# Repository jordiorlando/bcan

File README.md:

# bcan
### Beacon Controlled Autonomous Network

This project aims to create a semi-autonomous model train capable of detecting and avoiding obstacles. It makes use of small IR beacons placed between the rails to transmit a unique ID that can be mapped to various train functions, such as speed or lighting.

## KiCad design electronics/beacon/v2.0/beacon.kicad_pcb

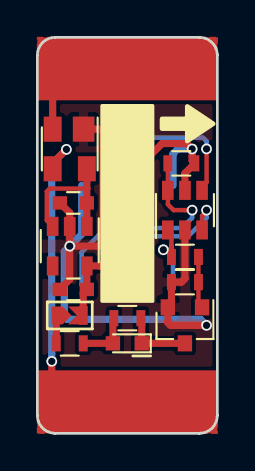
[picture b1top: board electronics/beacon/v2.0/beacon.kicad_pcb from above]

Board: 2 copper layers, 10.0 x 22.0 mm, 16 parts (1 on the bottom side), 13 nets.

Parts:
C1: 10u; C_0603
C2: 1u; C_0603
D1: IR; LED_0603
D2: BAS4002A; SOT-143
J1: L; Pad_Length10mm_Width3.5mm
J2: R; Pad_Length10mm_Width3.5mm
J3: TPI; Pin_Header_Straight_2x03_Pitch2.54mm_SMD
JP1: +1V8; Solder_Jumper_NC_Small
Q1: BSS138; SOT-23
R1, R3: 10k; R_0603
R2: 100; R_0603
R4: 47; R_0603
R5: R; R_0603
U1: ATTINY10-TS; SOT-23-6
U2: MIC5225-1.8YM5; SOT-23-5

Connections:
+1V8: C2.1, J3.2, JP1.2, R1.1, U1.5, U2.5
/PB0: J3.1, R2.1, U1.1
/PB1: J3.3, U1.3
/PB2: J3.4, U1.4
/RAIL_L: D2.2, J1.1
/RAIL_R: D2.3, J2.1
/~RST: J3.5, R1.2, U1.6
GND: C1.2, C2.2, D2.1, J3.6, Q1.2, R3.2, U1.2, U2.2
unnamed: D1.1, Q1.3, R5.2
unnamed: D1.2, R4.2, R5.1
unnamed: JP1.1, R4.1
unnamed: Q1.1, R2.2, R3.1
VCC: C1.1, D2.4, U2.1, U2.3

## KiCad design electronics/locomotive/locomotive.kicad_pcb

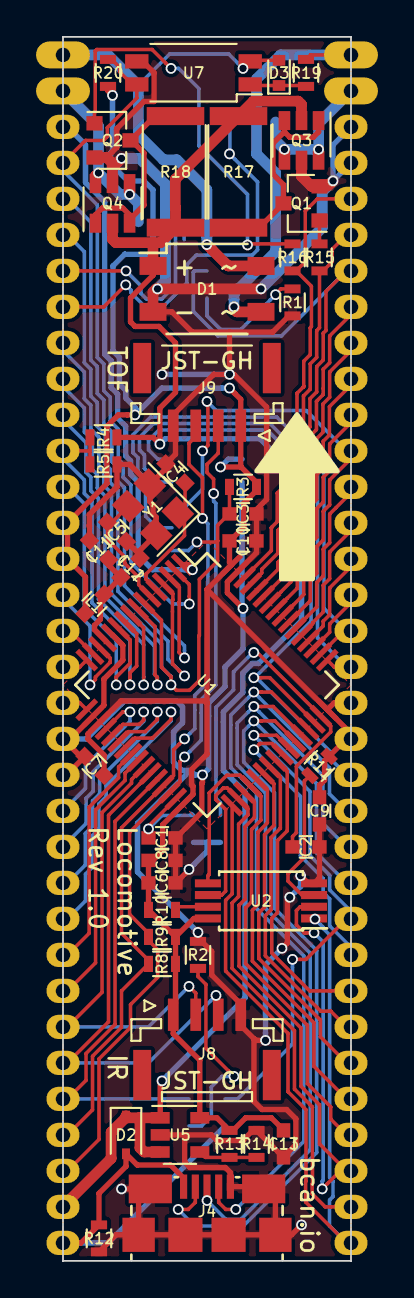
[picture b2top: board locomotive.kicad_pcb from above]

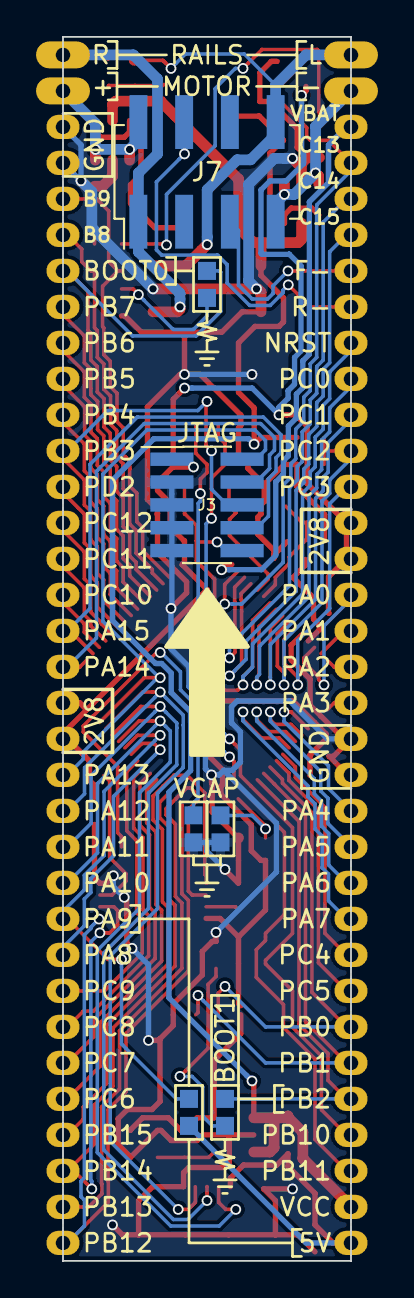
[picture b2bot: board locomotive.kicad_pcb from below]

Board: 2 copper layers, 16.0 x 68.0 mm, 58 parts (7 on the bottom side), 77 nets.

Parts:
C1, C2, C13: 2u2; C_0603
C3, C7, C8, C9, C10, C11: 100n; C_0603
C4, C5: 10p; C_0603
C6: 4u7; C_0603
C12: 1u; C_0603
D1: CDBHM240L-HF; TO-269AA
D2: CUS08F30; D_SOD-323
D3: 1N4148; D_SOD-523
J1: PIN[1..32]; Castellations_1x32_Pitch2.00mm
J2: PIN[33..64]; Castellations_1x32_Pitch2.00mm
J3: JTAG; Pin_Header_Straight_2x05_Pitch1.27mm_SMD
J4: USB_OTG; USB_Micro-B_Amphenol_10118192
J5: RAILS; Castellations_1x02_Pitch2.00mm
J6: MOTOR; Castellations_1x02_Pitch2.00mm
J7: TRAIN; Pin_Header_Straight_2x04_Pitch2.54mm_SMD
J8: IR; JST_GH_BM04B-GHS-TBT_04x1.25mm_Straight
J9: TOF; JST_GH_SM04B-GHS-TB_04x1.25mm_Angled
JP1: BOOT0; Solder_Jumper_NC
JP2: BOOT1; Solder_Jumper_NC
JP3: VCAP1; Solder_Jumper_NO
JP4: VCAP2; Solder_Jumper_NO
JP5: USB_VBUS; Solder_Jumper_NC
L1: 600; C_0603
Q1, Q2: MMBT2222A; SOT-23
Q3, Q4: DMG6601LVT; SOT-23-6
R1, R2, R3, R10, R11, R12, R20: 10k; R_0603
R4: 13k3; R_0603
R5: 2k8; R_0603
R8, R9: 4k7; R_0603
R13: 33k2; R_0603
R14: 26k1; R_0603
R15, R16: 1k; R_0603
R17, R18: 100; R_2512
R19: 1k5; R_0603
U1: STM32F405RGTx; TQFP-64_10x10mm_Pitch0.5mm
U2: M95512-RDW6TP; TSSOP-8_4.4x3mm_Pitch0.65mm
U5: SPX3819M5; SOT-23-5
U7: TLP293; SOP-4_4.4x2.8mm_Pitch1.27mm
Y1: 16MHz; Crystal_SMD_3225-4pin_3.2x2.5mm

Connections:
2V8: C6.1, C7.1, C8.1, C9.1, C10.1, C13.1, J1.12, J1.13, J2.15, J2.16, J3.1, J8.1, J9.1, L1.1, R3.1, R8.1, R9.1, R10.1, R11.1, R13.1, R20.1, U1.19, U1.32, U1.48, U1.64, U2.8, U5.5
+5V: D2.2, J1.32, J4.1, JP5.1, R12.1
/Controller/PH0: C4.1, U1.5, Y1.1
/Controller/PH1: C5.1, U1.6, Y1.3
/Controller/VCAP1: C1.1, JP3.2, U1.31
/Controller/VCAP2: C2.1, JP4.2, U1.47
/Controller/VDDA: C11.1, C12.1, L1.2, U1.13
BOOT0: J2.28, JP1.1, U1.60
FRONT-: J1.5, J7.5
GND: C1.2, C2.2, C3.2, C4.2, C5.2, C6.2, C7.2, C8.2, C9.2, C10.2, C11.2, C12.2, C13.2, D1.2, J1.18, J1.19, J2.31, J2.32, J3.3, J3.5, J3.7, J3.9, J4.5, J4.6, J8.4, J9.4, JP3.1, JP4.1, Q1.2, Q2.2, Q3.5, Q4.5, R1.2, R2.2, R5.2, R12.2, R14.2, U1.12, U1.18, U1.63, U2.4, U5.2, U7.3, Y1.2, Y1.4
MOT+: J6.1, J7.2, Q3.4, Q3.6
MOT-: J5.2, J7.7, Q4.4, Q4.6
NRST: C3.1, J1.7, J3.10, R3.2, U1.7
unnamed: D3.1, R19.1, U7.1
unnamed: JP1.2, R1.1
unnamed: JP2.2, R2.1
unnamed: Q1.1, R15.1
unnamed: Q1.3, Q3.1, Q3.3, R17.2
unnamed: Q2.1, R16.1
unnamed: Q2.3, Q4.1, Q4.3, R18.2
unnamed: R10.2, U2.7
unnamed: R11.2, U2.3
unnamed: R13.2, R14.1, U5.4
PA0: J1.14, U1.14
PA1: J1.15, U1.15
PA2: J1.16, U1.16
PA3: J1.17, U1.17
PA4: J1.20, U1.20
PA5: J1.21, U1.21
PA6: J1.22, U1.22
PA7: J1.23, U1.23
PA8: J2.9, U1.41
PA9: J2.10, JP5.2, U1.42
PA10: J2.11, J4.2, U1.43
PA11: J2.12, J4.3, U1.44
PA12: J2.13, J4.4, U1.45
PA13: J2.14, J3.2, U1.46
PA14: J2.17, J3.4, U1.49
PA15: J2.18, J3.8, U1.50
PB0: J1.26, J8.2, U1.26
PB1: J1.27, J8.3, U1.27
PB2: J1.28, JP2.1, U1.28
PB3: J2.23, J3.6, U1.55
PB4: J2.24, U1.56
PB5: J2.25, U1.57
PB6: J2.26, U1.58
PB7: J2.27, U1.59
PB8: J2.29, R15.2, U1.61
PB9: J2.30, R16.2, U1.62
PB10: J1.29, J9.3, R8.2, U1.29
PB11: J1.30, J9.2, R9.2, U1.30
PB12: J2.1, U1.33, U2.1
PB13: J2.2, U1.34, U2.6
PB14: J2.3, U1.35, U2.2
PB15: J2.4, U1.36, U2.5
PC0: J1.8, U1.8
PC1: J1.9, U1.9
PC2: J1.10, R4.2, R5.1, U1.10
PC3: J1.11, U1.11
PC4: J1.24, U1.24
PC5: J1.25, U1.25
PC6: J2.5, U1.37
PC7: J2.6, U1.38
PC8: J2.7, U1.39
PC9: J2.8, U1.40
PC10: J2.19, U1.51
PC11: J2.20, U1.52
PC12: J2.21, U1.53
PC13: J1.2, R20.2, U1.2, U7.4
PC14: J1.3, U1.3
PC15: J1.4, U1.4
PD2: J2.22, U1.54
RAIL_L: D1.4, D3.2, J5.1, J7.8, U7.2
RAIL_R: D1.3, J6.2, J7.1, R19.2
REAR-: J1.6, J7.4
VBAT: J1.1, U1.1
VCC: D1.1, D2.1, J1.31, Q3.2, Q4.2, R4.1, R17.1, R18.1, U5.1, U5.3

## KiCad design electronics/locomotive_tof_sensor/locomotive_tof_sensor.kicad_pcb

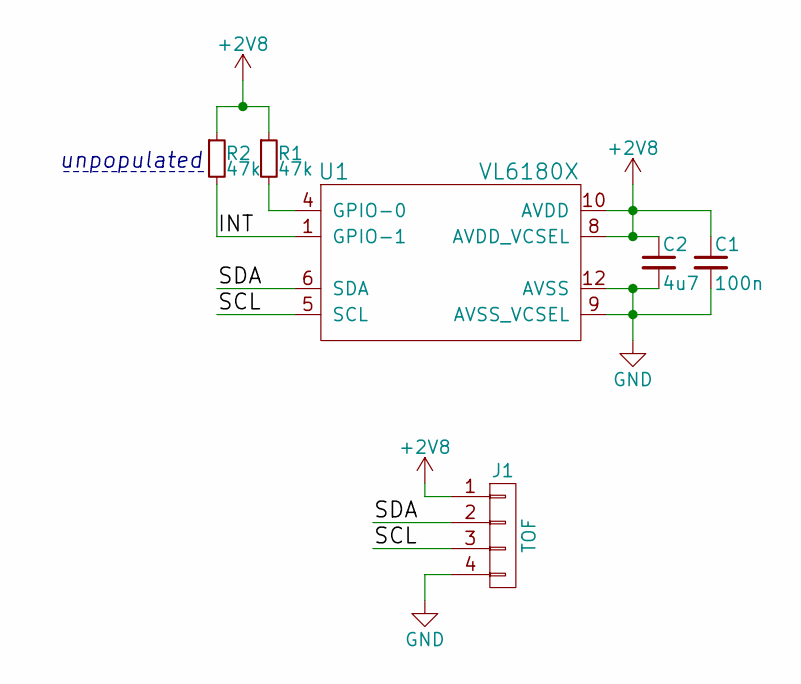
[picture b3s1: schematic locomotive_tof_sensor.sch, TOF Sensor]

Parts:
C1: 100n; C_0603
C2: 4u7; C_0603
J1: TOF; JST_GH_BM04B-GHS-TBT_04x1.25mm_Straight
R1, R2: 47k; R_0603
U1: VL6180X

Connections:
+2V8: C1.1, C2.1, J1.1, R1.1, R2.1, U1.8 (AVDD_VCSEL), U1.10 (AVDD)
/INT: R2.2, U1.1 (GPIO-1)
/SCL: J1.3, U1.5 (SCL)
/SDA: J1.2, U1.6 (SDA)
GND: C1.2, C2.2, J1.4, U1.9 (AVSS_VCSEL), U1.12 (AVSS)
unnamed: R1.2, U1.4 (GPIO-0)

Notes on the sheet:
unpopulated

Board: 2 copper layers, 6 parts (1 on the bottom side), 6 nets, no tracks yet.

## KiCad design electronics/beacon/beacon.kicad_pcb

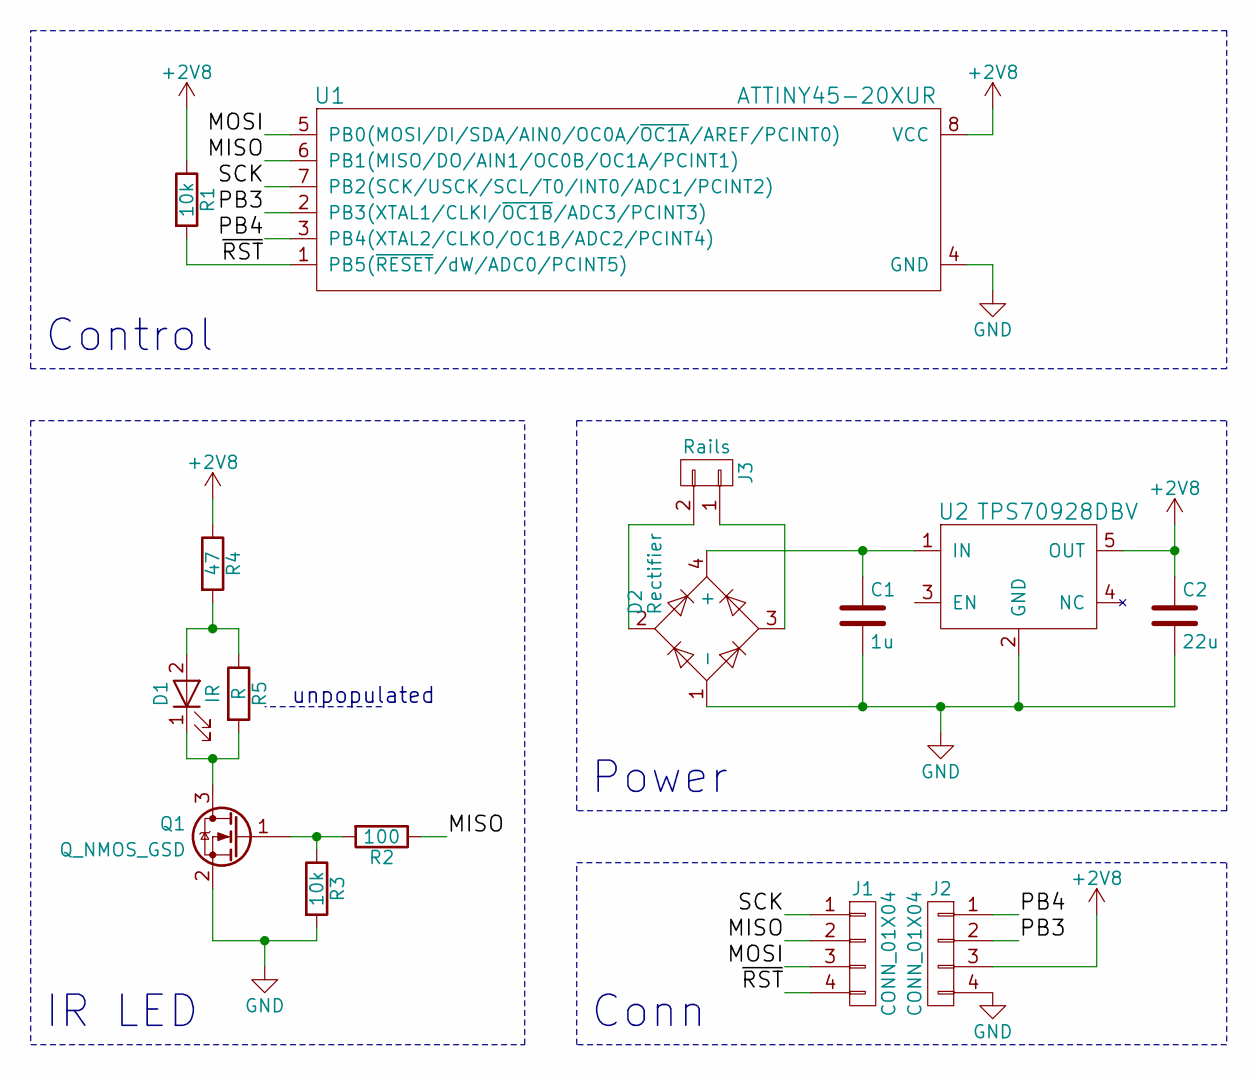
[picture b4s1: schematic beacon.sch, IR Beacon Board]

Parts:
C1: 1u; C_0603
C2: 22u; C_0603
D1: IR; LED_0603
D2: Rectifier; SOT-143
J1, J2: CONN_01X04; Edge_Connector_1x04_Pitch2.54mm_SMD
J3: Rails; HO_Rail_2_Length2.4mm_Width4mm
Q1: Q_NMOS_GSD; SOT-23
R1, R3: 10k; R_0603
R2: 100; R_0603
R4: 47; R_0603
R5: R; R_0603
U1: ATTINY45-20XUR; TSSOP-8_4.4x3mm_Pitch0.65mm
U2: TPS70928DBV; SOT-23-5

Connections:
+2V8: C2.1, J2.3, R1.1, R4.1, U1.8 (VCC), U2.5 (OUT)
/MISO: J1.2, R2.1, U1.6 (PB1(MISO/DO/AIN1/OC0B/OC1A/PCINT1))
/MOSI: J1.3, U1.5 (PB0(MOSI/DI/SDA/AIN0/OC0A/~OC1A~/AREF/P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)
/PB3: J2.2, U1.2 (PB3(XTAL1/CLKI/~OC1B~/ADC3/PCINT3))
/PB4: J2.1, U1.3 (PB4(XTAL2/CLKO/OC1B/ADC2/PCINT4))
/SCK: J1.1, U1.7 (PB2(SCK/USCK/SCL/T0/INT0/ADC1/PCINT2))
/~RST: J1.4, R1.2, U1.1 (PB5(~RESET~/dW/ADC0/PCINT5))
GND: C1.2, C2.2, D2.1 (-), J2.4, Q1.2 (S), R3.2, U1.4 (GND), U2.2 (GND)
unnamed: C1.1, D2.4 (+), U2.1 (IN)
unnamed: D1.1 (K), Q1.3 (D), R5.2
unnamed: D1.2 (A), R4.2, R5.1
unnamed: D2.2, J3.2
unnamed: D2.3, J3.1
unnamed: Q1.1 (G), R2.2, R3.1

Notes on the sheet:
unpopulated
Control
Power
IR LED
Conn

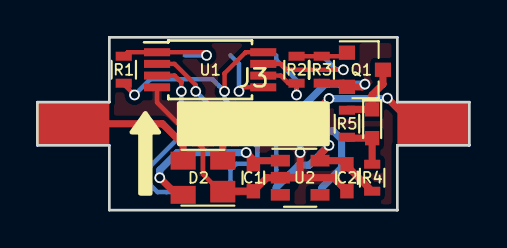
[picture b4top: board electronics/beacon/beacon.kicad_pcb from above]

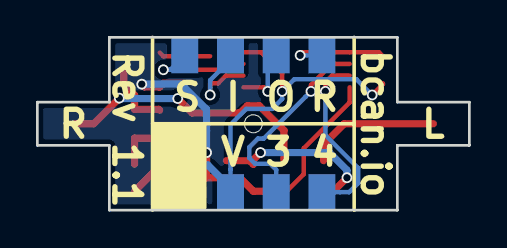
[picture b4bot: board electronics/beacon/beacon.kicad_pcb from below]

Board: 2 copper layers, 24.0 x 9.6 mm, 15 parts (2 on the bottom side), 14 nets.

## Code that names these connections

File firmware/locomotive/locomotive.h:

#ifndef LOCOMOTIVE_H
#define LOCOMOTIVE_H

#include <stdlib.h>
#include <stdbool.h>
#include <stdio.h>
#include <libopencm3/stm32/gpio.h>

typedef uint8_t pin_type;

static const uint32_t ports[4] = {
	GPIOA,
	GPIOB,
	GPIOC,
	GPIOD,
};

#define PA0  0x00
#define PA1  0x01
#define PA2  0x02
#define PA3  0x03
#define PA4  0x04
#define PA5  0x05
#define PA6  0x06
#define PA7  0x07
#define PA8  0x08
#define PA9  0x09
#define PA10 0x0A
#define PA11 0x0B
#define PA12 0x0C
#define PA13 0x0D
#define PA14 0x0E
#define PA15 0x0F
#define PB0  0x10
#define PB1  0x11
#define PB2  0x12
#define PB3  0x13
#define PB4  0x14
#define PB5  0x15
#define PB6  0x16
#define PB7  0x17
#define PB8  0x18
#define PB9  0x19
#define PB10 0x1A
#define PB11 0x1B
#define PB12 0x1C
#define PB13 0x1D
#define PB14 0x1E
#define PB15 0x1F
#define PC0  0x20
#define PC1  0x21
#define PC2  0x22
#define PC3  0x23
#define PC4  0x24
#define PC5  0x25
#define PC6  0x26
#define PC7  0x27
#define PC8  0x28
#define PC9  0x29
#define PC10 0x2A
#define PC11 0x2B
#define PC12 0x2C
#define PC13 0x2D
#define PC14 0x2E
#define PC15 0x2F
#define PD2  0x32

#define PORT(p) ports[p >> 4]
#define PIN(p) (1 << (p & 0x0F))


void print(char *str);
void println(char *str);

#endif

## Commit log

2017-02-16 Initial beacon AVR firmware
2017-02-16 Define CPU frequency in Makefile
2017-02-16 Specify the unique ID in the make command
2017-02-16 Implement code based on NEC IR protocol
2017-02-16 Switch from 24-bit to 16-bit IDs
2017-02-16 Add 'make fuses' rule
2017-02-17 Simplify delay function
2017-02-17 Add rails and mark IR shunt resistor as unpopulated
2017-02-19 Initial ARM setup using libopencm3
2017-02-19 Add USB MSC example from libopencm3
2017-02-19 Switch from NEC to custom IR protocol
    Uses Manchester encoding to ensure equal packet lengths and regular transitions
2017-02-19 Remove implicitly installed dependency
2017-02-22 Add library: TPS709xxDBV and ATTINY45-20XUR
2017-02-22 Finalize beacon schematic
2017-02-22 Begin beacon board layout
2017-02-22 Add OpenSCAD model of Atlas HO Code 83 track
    Dimensions were measured with calipers, might be inaccurate
2017-02-22 Add basic locomotive firmware readme
2017-02-23 First prototype beacon configurator
2017-02-24 Add beacon mappings spec
2017-02-24 Initial beacon reader pseudocode
2017-02-26 Add lib parts: BD3575HFP-TR, M95512-RDW6TP, ZXMHC6A07N8TC
2017-02-26 Finalize beacon schematic for initial run
2017-02-27 Complete configurator functionality
2017-02-28 Initial locomotive electronic design
2017-02-28 Rearrange spec directory
2017-02-28 Initial beacon IR protocol spec
2017-03-08 firmware: locomotive: Finish environment setup
2017-03-08 firmware: locomotive: Fix rcc clock setup for 2.8V
2017-03-08 firmware: locomotive: Update submodules
2017-03-08 firmware: locomotive: Update evq submodule
2017-03-09 firmware: locomotive: Fix RAM size
2017-03-09 firmware: locomotive: Build evq submodule
2017-03-09 firmware: locomotive: Add systick blink for STM32-H405
2017-03-10 firmware: locomotive: Update readme
2017-03-10 firmware: locomotive: Capture button press with EXTI
2017-03-11 Update bcan.bak
    Added SPX3819M5-L/TR, DMG6601LVT-7, ACPL-M21L-500E
2017-03-11 Added SPX3819M5-L/TR, DMG6601LVT-7, ACPL-M21L-500E
    Added SPX3819M5-L/TR, DMG6601LVT-7, ACPL-M21L-500E
2017-03-11 Updated schematics
    voltage regulator, TOF, IR receiver, voltage scaler, I2C control lines, power
2017-03-11 Updated schematics
2017-03-11 Update schematics
    changed voltage regulator resistor values
2017-03-13 electronics: lib: Add rail and edge connector footprints
2017-03-13 electronics: beacon: WIP 3.5x28 board layout
2017-03-13 mechanical: Add locomotive PCB 3D model
2017-03-13 firmware: locomotive: Clean up blinky code
2017-03-15 firmware: locomotive: Implement beacon reader
    Uses Timer 3 input capture to detect edges and keep track of pulse lengths. Currently untested.
2017-03-15 firmware: locomotive: Add missing definition
    Temporary fix until change is pulled upstream
2017-03-16 firmware: locomotive: Break blinky into separate source
2017-03-16 firmware: locomotive: Tweak and fix some beacon code
    Still completely broken
2017-03-17 electronics: beacon: Final beacon board Rev 1.0
    - increase board size to fit all components
    - add rail and connector footprints to library
    - improve track mechanical model
2017-03-17 electronics: beacon: Final beacon board Rev 1.1
    - widened track solder tabs
    - improved schematic/board images
2017-03-17 electronics: beacon: Tweak beacon board Rev 1.1
    - increase silkscreen arrow size
    - remove errant J3 silkscreen reference
    - fix PCB colors & thickness
2017-03-17 electronics: lib: Add vreg, mosfets, optoisolator
    SPX3819M5-L/TR, DMG6601LVT-7, ACPL-M21L-500E
2017-03-17 firmware: locomotive: Change voltage regulator resistor values
2017-03-17 electronics: locomotive: Update schematics
    Voltage regulator, TOF, IR receiver, voltage scaler, I2C control lines, power
2017-03-21 electronics: lib: Add Acronet KiCAD Libraries
2017-03-21 electronics: beacon: Improve schematic labeling & readability
2017-03-21 electronics: lib: Add TSOP572xx footprint
2017-03-21 electronics: locomotive_ir_receiver: Board Rev 1.0
2017-03-21 electronics: lib: Tweak TSOP572xx F.Fab
2017-03-21 electronics: lib: Add VL6180X footprint
2017-03-21 electronics: locomotive_tof_sensor: Initial commit
2017-03-21 electronics: bachmann_H633Y: Initial commit
    Reverse-engineered Bachmann HO EMD GP38-2 PCB
2017-03-21 mechanical: Fix locomotive PCB holes
2017-03-22 electronics: locomotive_tof_sensor: Board Rev 1.0
2017-03-22 electronics: locomotive: Fix up schematics
    - add all parts and label them
    - some values still tentative
    - still need to finish connectors
2017-03-22 electronics: beacon: Remove duplicate library path
2017-03-25 firmware: beacon: Change default programmer
    avrisp2 -> usbasp
2017-03-25 Clarify README
2017-03-25 spec: locomotive_config: Update spec
    - add direction control
    - improve explanation of direction bits
2017-03-26 Update instruction input to match specification
    Speed was improperly numbered, and direction was missing
2017-03-26 electronics: beacon: Update schematic date and image
2017-03-26 electronics: beacon: Add PNG schematic/board images
2017-03-31 electronics: lib: Add footprints
    - castellations
    - solder jumpers
    - bridge rectifier (TO-269AA)
    - USB Micro-B connector
2017-03-31 electronics: locomotive: Board Rev 1.0
2017-03-31 electronics: Clean up schematic images
2017-03-31 firmware: locomotive: Update submodule libopencm3
2017-04-01 firmware: beacon: General clean-up
2017-04-03 firmware: locomotive: Make clean now cleans subdirs
2017-04-03 firmware: locomotive: Update submodule evq
2017-04-10 firmware: locomotive: Fix beacon code
    Forgot to enable RCC peripheral clock for GPIOB...
2017-04-11 firmware: locomotive: Basic TOF complete
2017-04-11 firmware: locomotive: Tested and working TOF code
2017-04-14 firmware: locomotive: Add blink_on and blink_off
2017-04-14 firmware: locomotive: Use beacon code
2017-04-14 mechanical: Add rail image
2017-04-14 firmware: locomotive: Add WIP beacon tester
2017-04-14 Add beacon protocol visualizer
2017-04-17 firmware: locomotive: Rename blink to led & generalize it
2017-04-17 firmware: locomotive: Refactor tof code
    - replace tof_should_stop() with tof_distance()
2017-04-17 firmware: locomotive: Refactor beacon code
2017-04-21 firmware: locomotive: Add USART serial print
2017-04-21 firmware: locomotive: Added rom for saving/loading mappings
2017-04-21 firmware: locomotive: Rename rom to flash
2017-04-21 firmware: locomotive: Added ramdisk_write
2017-04-21 firmware: locomotive: Added flash test
2017-04-21 firmware: locomotive: Split out flash_load from flash_setup
2017-04-21 firmware: locomotive: Fixed flash test to not use id 0
2017-04-21 firmware: locomotive: Fix blink->led_blink
2017-04-21 firmware: locomotive: Added printing to flash test
2017-04-21 test
2017-04-21 cleanup flash code
2017-04-24 firmware: locomotive: Motor PWM and ADC code
2017-04-24 firmware: locomotive: Add led_toggle()
2017-04-24 firmware: locomotive: Use beacon_t struct
2017-04-24 firmware: locomotive: Motor, mappings, & serial code
    - parse beacon IDs and match to stored mappings
    - set motor speed/direction based upon current track voltage and target speed
    - implement a simple USART print() and println() for debugging
2017-04-24 Add atom-build config for in-editor building
2017-04-24 spec: beacon_protocol: Fix incorrect manchester code
2017-04-24 electronics: Re-label Bachmann L+ to Io
2017-04-25 firmware: locomotive: Fix and test beacon code
    TODO: figure out how to reduce the required number of edges
2017-04-27 electronics: locomotive: Fix mislabeled parts
2017-04-28 electronics: beacon: Move v1.1 into subfolder
2017-04-28 electronics: beacon: Add v2.0 hardware
    Have yet to determine current-limiting resistor value
2017-05-04 docs: Add preliminary final report
2017-05-04 docs: Complete final report
2017-05-04 electronics: beacon: Add solder jumper to v2.0
2017-05-04 electronics: bachmann_H633Y: Add CircuitJS simulation
2017-05-08 firmware: beacon: Prepare for v2 firmware
2017-05-08 firmware: beacon: Add v2 firmware
    Switch from ATtiny45 to ATtiny10
2017-12-26 electronics: Rearrange folder structure
2017-12-26 electronics: beacon: Add v0.2 datasheets
2017-12-26 electronics: beacon: Add old ID labels
2017-12-26 Edit atom-build config
2017-12-26 electronics: lib: Add footprints
    - Pad_Length6mm_Width3.5mm
2017-12-26 electronics: lib: Add symbols
    - ATTINY10-TS
    - DRV8801PWR
    - MC33931EK
2017-12-26 Update gitignore
